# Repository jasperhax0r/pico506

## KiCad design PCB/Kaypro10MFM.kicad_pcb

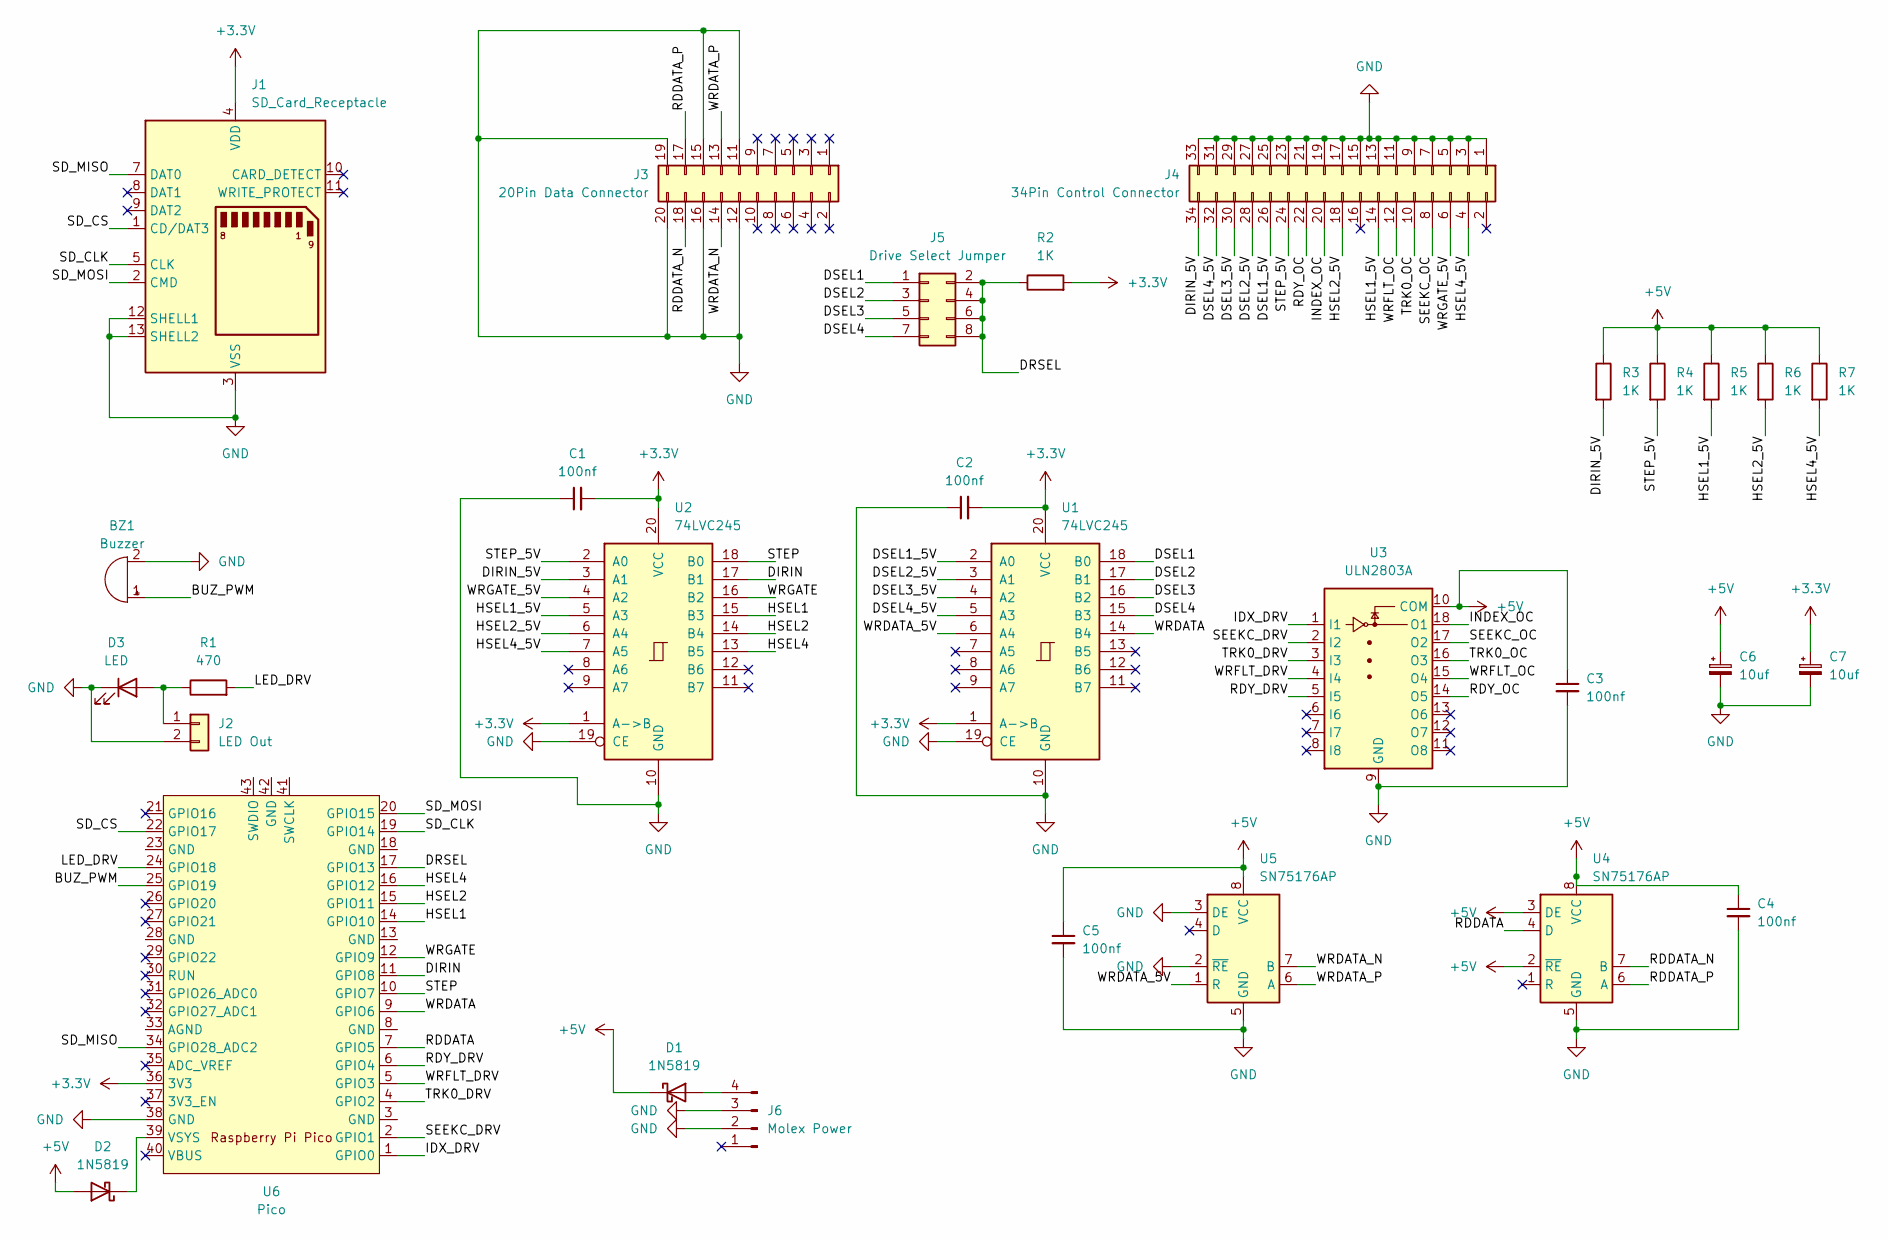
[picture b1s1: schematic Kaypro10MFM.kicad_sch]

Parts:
BZ1: Buzzer; Buzzer_12x9.5RM7.6
C1, C2, C3, C4, C5: 100nf; C_Disc_D5.0mm_W2.5mm_P5.00mm
C6, C7: 10uf; CP_Radial_D5.0mm_P2.50mm
D1, D2: 1N5819; D_DO-41_SOD81_P10.16mm_Horizontal
D3: LED; LED_D5.0mm
J1: SD_Card_Receptacle; SD_Hirose_DM1AA_SF_PEJ82
J2: LED Out; PinHeader_1x02_P2.54mm_Vertical
J3: 20Pin Data Connector; IDC-Header_2x10_P2.54mm_Vertical
J4: 34Pin Control Connector; IDC-Header_2x17_P2.54mm_Vertical
J5: Drive Select Jumper; IDC-Header_2x04_P2.54mm_Vertical
J6: Molex Power; TE_MATE-N-LOK_350211-1_1x04_P5.08mm_Vertical
R1: 470; R_Axial_DIN0207_L6.3mm_D2.5mm_P10.16mm_Horizontal
R2, R3, R4, R5, R6, R7: 1K; R_Axial_DIN0207_L6.3mm_D2.5mm_P10.16mm_Horizontal
U1, U2: 74LVC245; DIP-20_W7.62mm
U3: ULN2803A; DIP-18_W7.62mm
U4, U5: SN75176AP; DIP-8_W7.62mm
U6: Pico; RPi_Pico_SMD_TH

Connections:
+3.3V: C1.2, C2.2, C7.1, J1.4 (VDD), R2.2, U1.1 (A->B), U1.20 (VCC), U2.1 (A->B), U2.20 (VCC), U6.36 (3V3)
+5V: C3.1, C4.1, C5.1, C6.1, D1.1 (K), D2.2 (A), R3.1, R4.1, R5.1, R6.1, R7.1, U3.10 (COM), U4.2 (~RE), U4.3 (DE), U4.8 (VCC), U5.8 (VCC)
/BUZ_PWM: BZ1.1 (+), U6.25 (GPIO19)
/DIRIN: U2.17 (B1), U6.11 (GPIO8)
/DIRIN_5V: J4.34, R3.2, U2.3 (A1)
/DRSEL: J5.2, J5.4, J5.6, J5.8, R2.1, U6.17 (GPIO13)
/DSEL1: J5.1, U1.18 (B0)
/DSEL1_5V: J4.26, U1.2 (A0)
/DSEL2: J5.3, U1.17 (B1)
/DSEL2_5V: J4.28, U1.3 (A1)
/DSEL3: J5.5, U1.16 (B2)
/DSEL3_5V: J4.30, U1.4 (A2)
/DSEL4: J5.7, U1.15 (B3)
/DSEL4_5V: J4.32, U1.5 (A3)
/HSEL1: U2.15 (B3), U6.14 (GPIO10)
/HSEL1_5V: J4.14, R5.2, U2.5 (A3)
/HSEL2: U2.14 (B4), U6.15 (GPIO11)
/HSEL2_5V: J4.18, R6.2, U2.6 (A4)
/HSEL4: U2.13 (B5), U6.16 (GPIO12)
/HSEL4_5V: J4.4, R7.2, U2.7 (A5)
/IDX_DRV: U3.1 (I1), U6.1 (GPIO0)
/INDEX_OC: J4.20, U3.18 (O1)
/LED_DRV: R1.2, U6.24 (GPIO18)
/RDDATA: U4.4 (D), U6.7 (GPIO5)
/RDDATA_N: J3.18, U4.7 (B)
/RDDATA_P: J3.17, U4.6 (A)
/RDY_DRV: U3.5 (I5), U6.6 (GPIO4)
/RDY_OC: J4.22, U3.14 (O5)
/SD_CLK: J1.5 (CLK), U6.19 (GPIO14)
/SD_CS: J1.1 (CD/DAT3), U6.22 (GPIO17)
/SD_MISO: J1.7 (DAT0), U6.34 (GPIO28_ADC2)
/SD_MOSI: J1.2 (CMD), U6.20 (GPIO15)
/SEEKC_DRV: U3.2 (I2), U6.2 (GPIO1)
/SEEKC_OC: J4.8, U3.17 (O2)
/STEP: U2.18 (B0), U6.10 (GPIO7)
/STEP_5V: J4.24, R4.2, U2.2 (A0)
/TRK0_DRV: U3.3 (I3), U6.4 (GPIO2)
/TRK0_OC: J4.10, U3.16 (O3)
/WRDATA: U1.14 (B4), U6.9 (GPIO6)
/WRDATA_5V: U1.6 (A4), U5.1 (R)
/WRDATA_N: J3.14, U5.7 (B)
/WRDATA_P: J3.13, U5.6 (A)
/WRFLT_DRV: U3.4 (I4), U6.5 (GPIO3)
/WRFLT_OC: J4.12, U3.15 (O4)
/WRGATE: U2.16 (B2), U6.12 (GPIO9)
/WRGATE_5V: J4.6, U2.4 (A2)
GND: BZ1.2 (-), C1.1, C2.1, C3.2, C4.2, C5.2, C6.2, C7.2, D3.1 (K), J1.3 (VSS), J1.6 (VSS), J1.12 (SHELL1), J1.13 (SHELL2), J2.2, J3.11, J3.12, J3.15, J3.16, J3.19, J3.20, J4.1, J4.3, J4.5, J4.7, J4.9, J4.11, J4.13, J4.15, J4.17, J4.19, J4.21, J4.23, J4.25, J4.27, J4.29, J4.31, J4.33, J6.2, J6.3, U1.10 (GND), U1.19 (CE), U2.10 (GND), U2.19 (CE), U3.9 (GND), U4.5 (GND), U5.2 (~RE), U5.3 (DE), U5.5 (GND), U6.38 (GND)
unnamed: D1.2 (A), J6.4
unnamed: D2.1 (K), U6.39 (VSYS)
unnamed: D3.2 (A), J2.1, R1.1

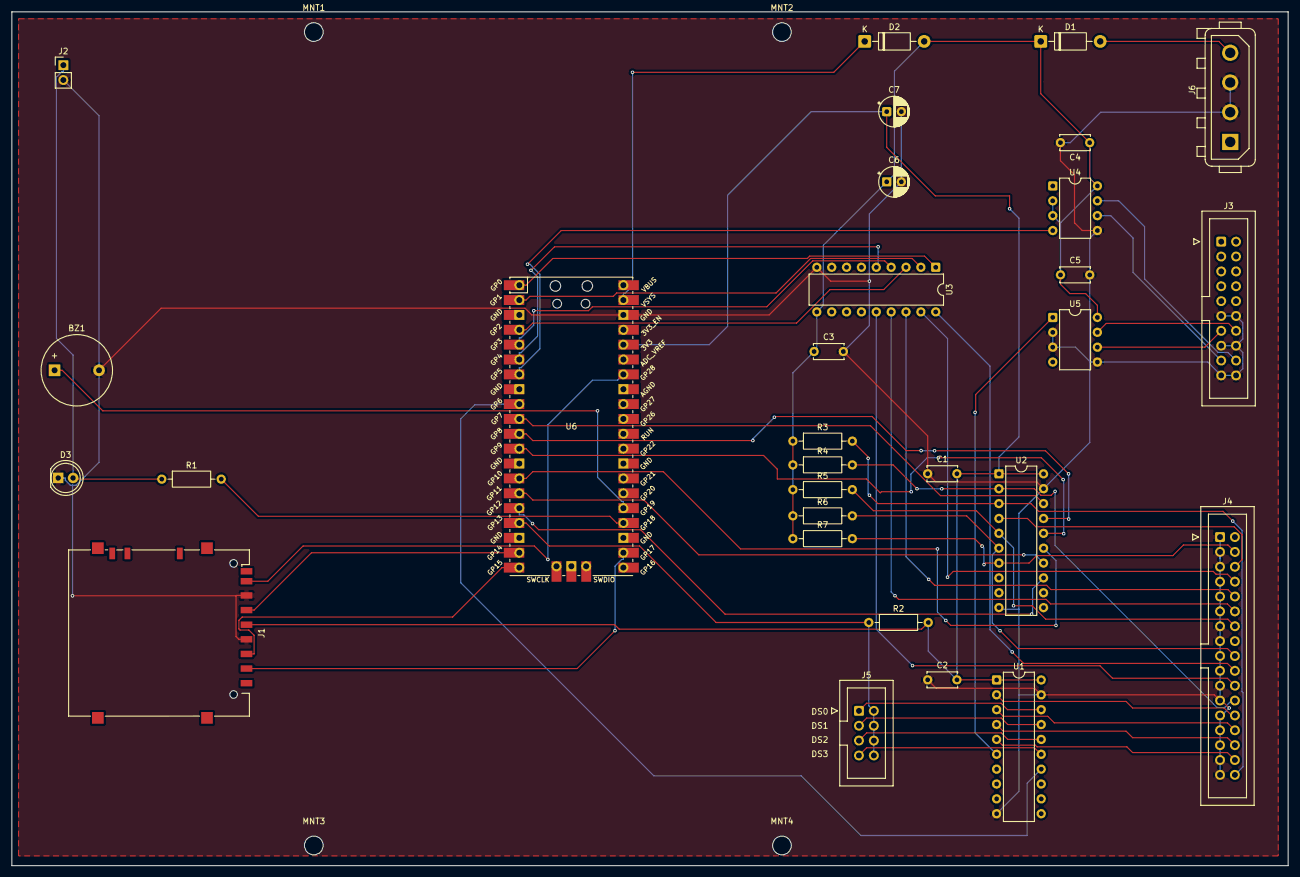
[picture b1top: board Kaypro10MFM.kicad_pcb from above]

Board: 2 copper layers, 218.1 x 145.9 mm, 34 parts (0 on the bottom side), 50 nets.

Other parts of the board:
MNT1, MNT2, MNT3, MNT4: MountingHole_3.2mm_M3

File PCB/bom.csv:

Designator,Footprint,Quantity,Value,LCSC Part #
BZ1,Buzzer_12x9.5RM7.6,1,Buzzer,
"C1, C2, C3, C4, C5",C_Disc_D5.0mm_W2.5mm_P5.00mm,5,100nf,
"C6, C7",CP_Radial_D5.0mm_P2.50mm,2,10uf,
"D1, D2",D_DO-41_SOD81_P10.16mm_Horizontal,2,1N5819,
D3,LED_D5.0mm,1,LED,
J1,SD_Hirose_DM1AA_SF_PEJ82,1,SD_Card_Receptacle,
J2,PinHeader_1x02_P2.54mm_Vertical,1,LED Out,
J3,IDC-Header_2x10_P2.54mm_Vertical,1,20Pin Data Connector,
J4,IDC-Header_2x17_P2.54mm_Vertical,1,34Pin Control Connector,
J5,IDC-Header_2x04_P2.54mm_Vertical,1,Drive Select Jumper,
J6,TE_MATE-N-LOK_350211-1_1x04_P5.08mm_Vertical,1,Molex Power,
R1,R_Axial_DIN0207_L6.3mm_D2.5mm_P10.16mm_Horizontal,1,470,
"R2, R3, R4, R5, R6, R7",R_Axial_DIN0207_L6.3mm_D2.5mm_P10.16mm_Horizontal,6,1K,
"U1, U2",DIP-20_W7.62mm,2,74LVC245,
U3,DIP-18_W7.62mm,1,ULN2803A,
"U4, U5",DIP-8_W7.62mm,2,SN75176AP,
U6,RPi_Pico_SMD_TH,1,Pico,

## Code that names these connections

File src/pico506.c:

// Copyright (c) Kuba Szczodrzyński 2025-8-4.

#include "pico506.h"

int main() {
	set_sys_clock_khz(200000, true);
	stdio_init_all();
        LT_I("BUILD %s %s", __DATE__, __TIME__);

	pico506_t *pico = malloc(sizeof(*pico));
	memset(pico, 0, sizeof(*pico));
        
	LT_D("Initializing SPI...");
	pico->storage.sd.spi.sck_pin = PIN_SD_SCK;
	pico->storage.sd.spi.tx_pin	 = PIN_SD_MOSI;
	pico->storage.sd.spi.rx_pin	 = PIN_SD_MISO;
	pico->storage.sd.spi.cs_pin	 = PIN_SD_CS;
	pico->storage.sd.spi.use_dma = true;
	sd_spi_init(&pico->storage.sd, 25 * 1000 * 1000);

	uint retry_ms = 5000;
	while (1) {
		if (storage_init(pico) != 0)
			goto retry;
		if (storage_open(pico, "/HDD.RLL") != 0)
			goto retry;

		if (pico->storage.file_size != DRIVE_BYTES) {
			LT_E("Image file size invalid, found %u bytes, expected %u bytes", pico->storage.file_size, DRIVE_BYTES);
			storage_close(pico);
			goto retry;
		}
		LT_I("Image file size OK");

		break;

	retry:
		LT_E("Retrying in %u ms...", retry_ms);
		sleep_ms(retry_ms);
	}

	st506_start(pico);

	LT_I(
		"Emulator initialized - C/H/S: %u/%u/%u, data rate: %.1f Mb/s",
		CYLINDERS,
		HEADS,
		SECTORS_PER_PULSE * PULSES_PER_TRACK,
		(double)DATA_RATE / 1e6
	);

	while (1) {
		st506_loop(pico);
	}
}
